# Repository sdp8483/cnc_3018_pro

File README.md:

# CNC 3018 Pro Router
Upgrades for the 3018 pro CNC router

https://samueldperry.com/cnc-3018-pro-router/

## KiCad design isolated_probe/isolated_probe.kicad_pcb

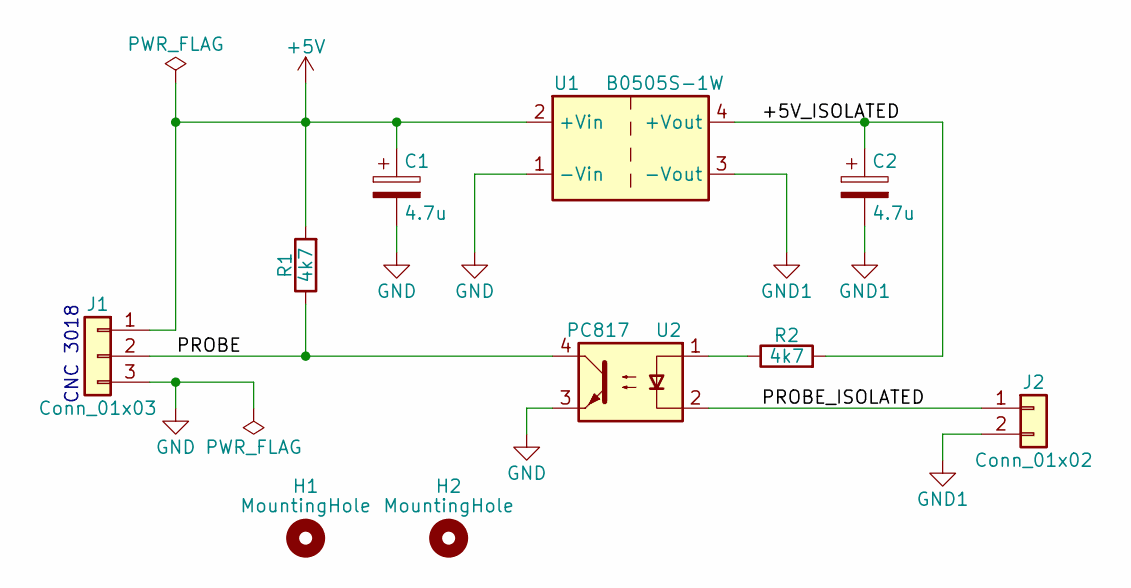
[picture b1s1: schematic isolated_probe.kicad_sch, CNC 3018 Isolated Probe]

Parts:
C1, C2: 4.7u; CP_Radial_D5.0mm_P2.50mm
H1, H2: MountingHole; MountingHole_3.2mm_M3
J1: Conn_01x03; PinHeader_1x03_P2.54mm_Vertical
J2: Conn_01x02; PinHeader_1x02_P2.54mm_Vertical
R1, R2: 4k7; R_Axial_DIN0204_L3.6mm_D1.6mm_P7.62mm_Horizontal
U1: B0505S-1W; Converter_DCDC_TRACO_TEA1-xxxx_THT
U2: PC817; DIP-4_W7.62mm

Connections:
+5V: C1.1, J1.1, R1.2, U1.2 (+Vin)
/+5V_ISOLATED: C2.1, R2.2, U1.4 (+Vout)
/PROBE: J1.2, R1.1, U2.4
/PROBE_ISOLATED: J2.1, U2.2
GND: C1.2, J1.3, U1.1 (-Vin), U2.3
GND1: C2.2, J2.2, U1.3 (-Vout)
unnamed: R2.1, U2.1

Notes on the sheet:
CNC 3018

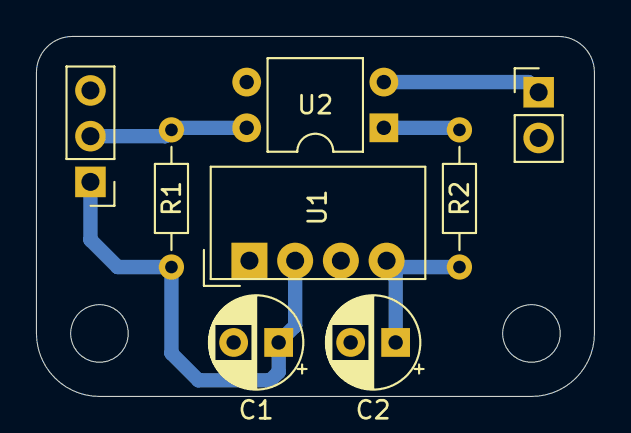
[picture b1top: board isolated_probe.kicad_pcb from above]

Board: 2 copper layers, 31.0 x 20.0 mm, 10 parts (0 on the bottom side), 7 nets.

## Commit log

2020-06-30 add endstop files
2020-07-01 add 3030 printed tee nut
2020-07-02 adjust printed tee nut dimensions
2020-07-04 lower feed rate by 80%
2020-07-05 machine holes deeper to go all the way through
2020-07-10 adjust thread hole size from 7.95 to 7.55 to fit tnuts
2020-07-10 reduce tnut hole diameter
2020-08-03 deeper notches
2020-08-03 fix 2020 mounting hole spacing
2020-08-07 fix base dims
2020-08-10 add link
2024-04-20 create resurfacing gcode generator
2024-12-11 ignore freecad backup files
2024-12-24 add drawings
2024-12-24 link to blog
2025-01-03 start parametric model
2025-01-25 init dir
2025-01-25 add #auto_saved_files#
2025-01-25 edit pcb name
2025-01-25 create B0505S-1W 3D model
2025-01-25 complete PCB layout
2025-01-26 move to dir
2025-01-27 export schematic to PDF
